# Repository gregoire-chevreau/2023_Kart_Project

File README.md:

# 2023_Kart_Project

Dans ce dossier GitHub, vous trouverez toutes les informations pour continuer le projet.
Ce dernier est composé d'une carte de commande avec la NUCLEO STM32G431RB ainsi que d'un onduleur.

## Table des matières

- [Cahier des charges](#charges)
- [PCB de commande](#commande)
- [Onduleur](#onduleur)
- [Code](#code)

## Cahier des charges

Le but est de faire rouler le kart à 20 km/h.
Le moteur est un moteur OZO 3500W à alimenter en 72 V (https://ozo-electric.com/fr/moteurs-centraux-brushless/679130-moteur-moto-3500w-electrique-central-brushless-bldc.html).
La batterie fourni une tension de  72V (https://ozo-electric.com/fr/72v/282892-batterie-72v-21ah-1512wh-pvc-panasonic-lithium.html#/285-connecteur_de_charge-anderson_pp30/282864-bms-60a_continu_250a_max_compatible_charge_rapide_10a/168358-connecteur_de_puissance-amass_xt90).

## PCB de commande

Ce PCB est composé de la carte NUCLEO, d'une isolation galvanique et d'un level-shifter.
L'isolation galvanique pourra disparaître pour faire un seul PCB commun par la suite. En effet, des optocoupleurs sont prévus comme driver de MOSFET.

## Onduleur

L'onduleur a les caractéristiques suivantes : 
- Tension d'alimentation : 72 V
- Courant nominal : 48 A
De plus, sur cette carte, nous avons prévu une alimentation 15V afin d'alimenter la carte de commande.

## Code

Le code est réalisé avec STM32CubeIDE.
Nous utilisons : 
- 6 sorties GPIO pour commander l’onduleur
- 3 entrées GPIO pour les capteurs Hall
- 1 entrée ADC pour le potentiomètre
- 1 entrée ADC pour le capteur de tension de la batterie
- 1 entrée ADC pour les capteurs de courant de phase

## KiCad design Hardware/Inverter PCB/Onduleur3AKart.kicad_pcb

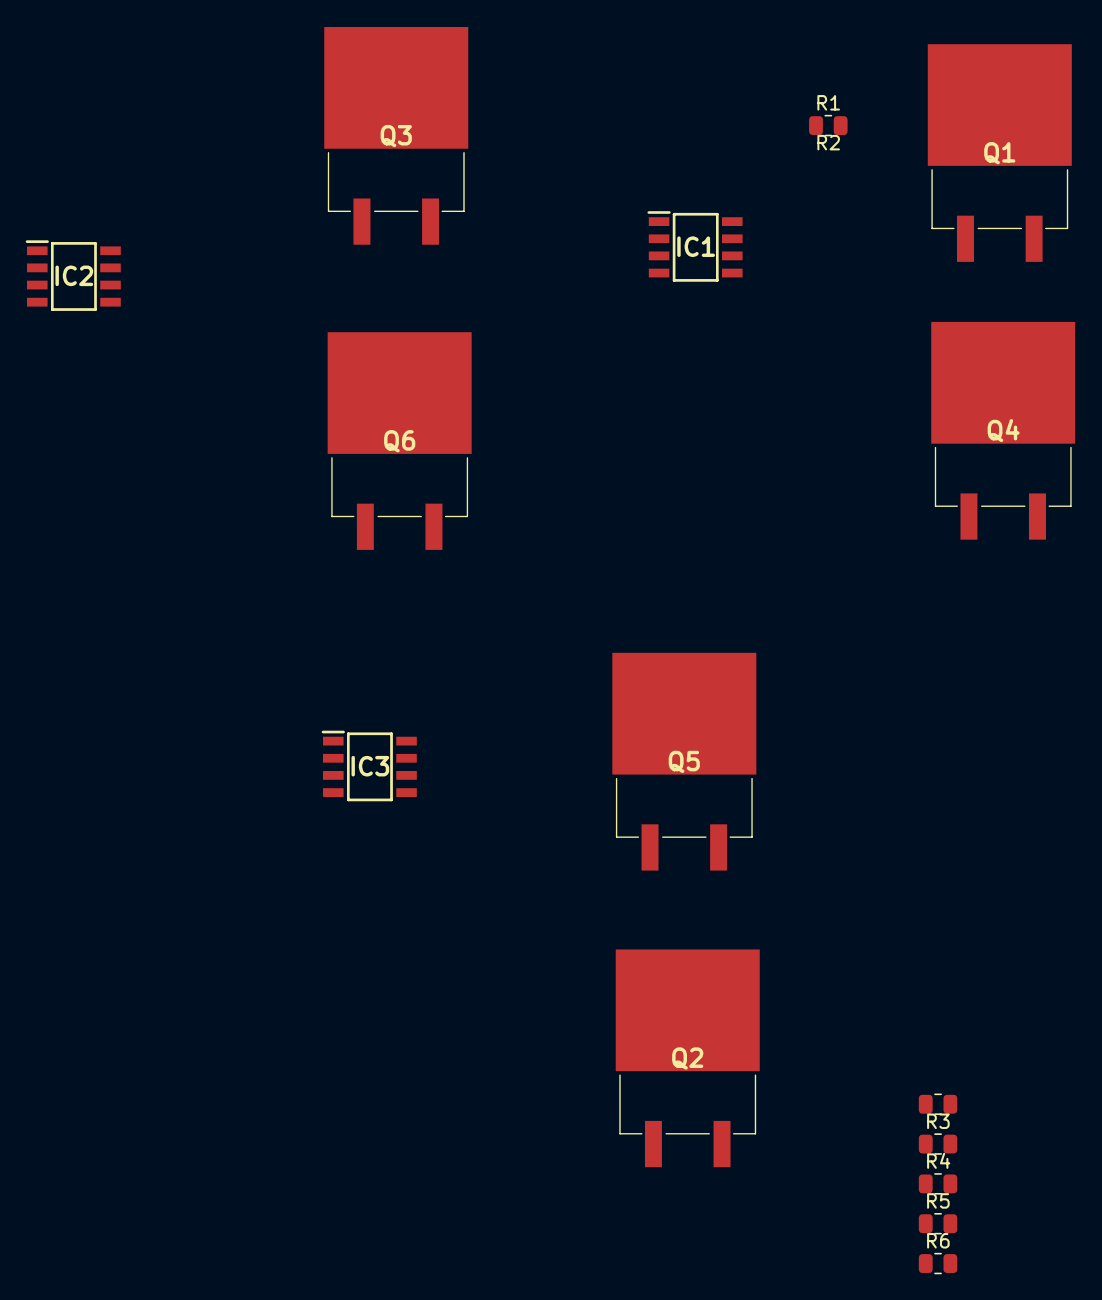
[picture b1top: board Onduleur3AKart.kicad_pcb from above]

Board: 2 copper layers, 15 parts (0 on the bottom side), 15 nets, no tracks yet.

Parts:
IC1, IC2, IC3: TPS2836DR
Q1, Q2, Q3, Q4, Q5, Q6: SUM60N10-17-E3; SUM60N1017E3
R1, R3, R5: 1; R_0805_2012Metric
R2, R4, R6: 5; R_0805_2012Metric

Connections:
unnamed: IC1.6 (BOOTLO), R2.1
unnamed: IC1.7 (HIGHDR), R1.1
unnamed: IC2.6 (BOOTLO), R4.1
unnamed: IC2.7 (HIGHDR), R3.1
unnamed: IC3.6 (BOOTLO), R6.1
unnamed: IC3.7 (HIGHDR), R5.1
unnamed: Q1.1 (G), R1.2
unnamed: Q1.3 (S), Q4.2 (D)
unnamed: Q2.1 (G), R3.2
unnamed: Q2.3 (S), Q5.2 (D)
unnamed: Q3.1 (G), R5.2
unnamed: Q3.3 (S), Q6.2 (D)
unnamed: Q4.1 (G), R2.2
unnamed: Q5.1 (G), R4.2
unnamed: Q6.1 (G), R6.2

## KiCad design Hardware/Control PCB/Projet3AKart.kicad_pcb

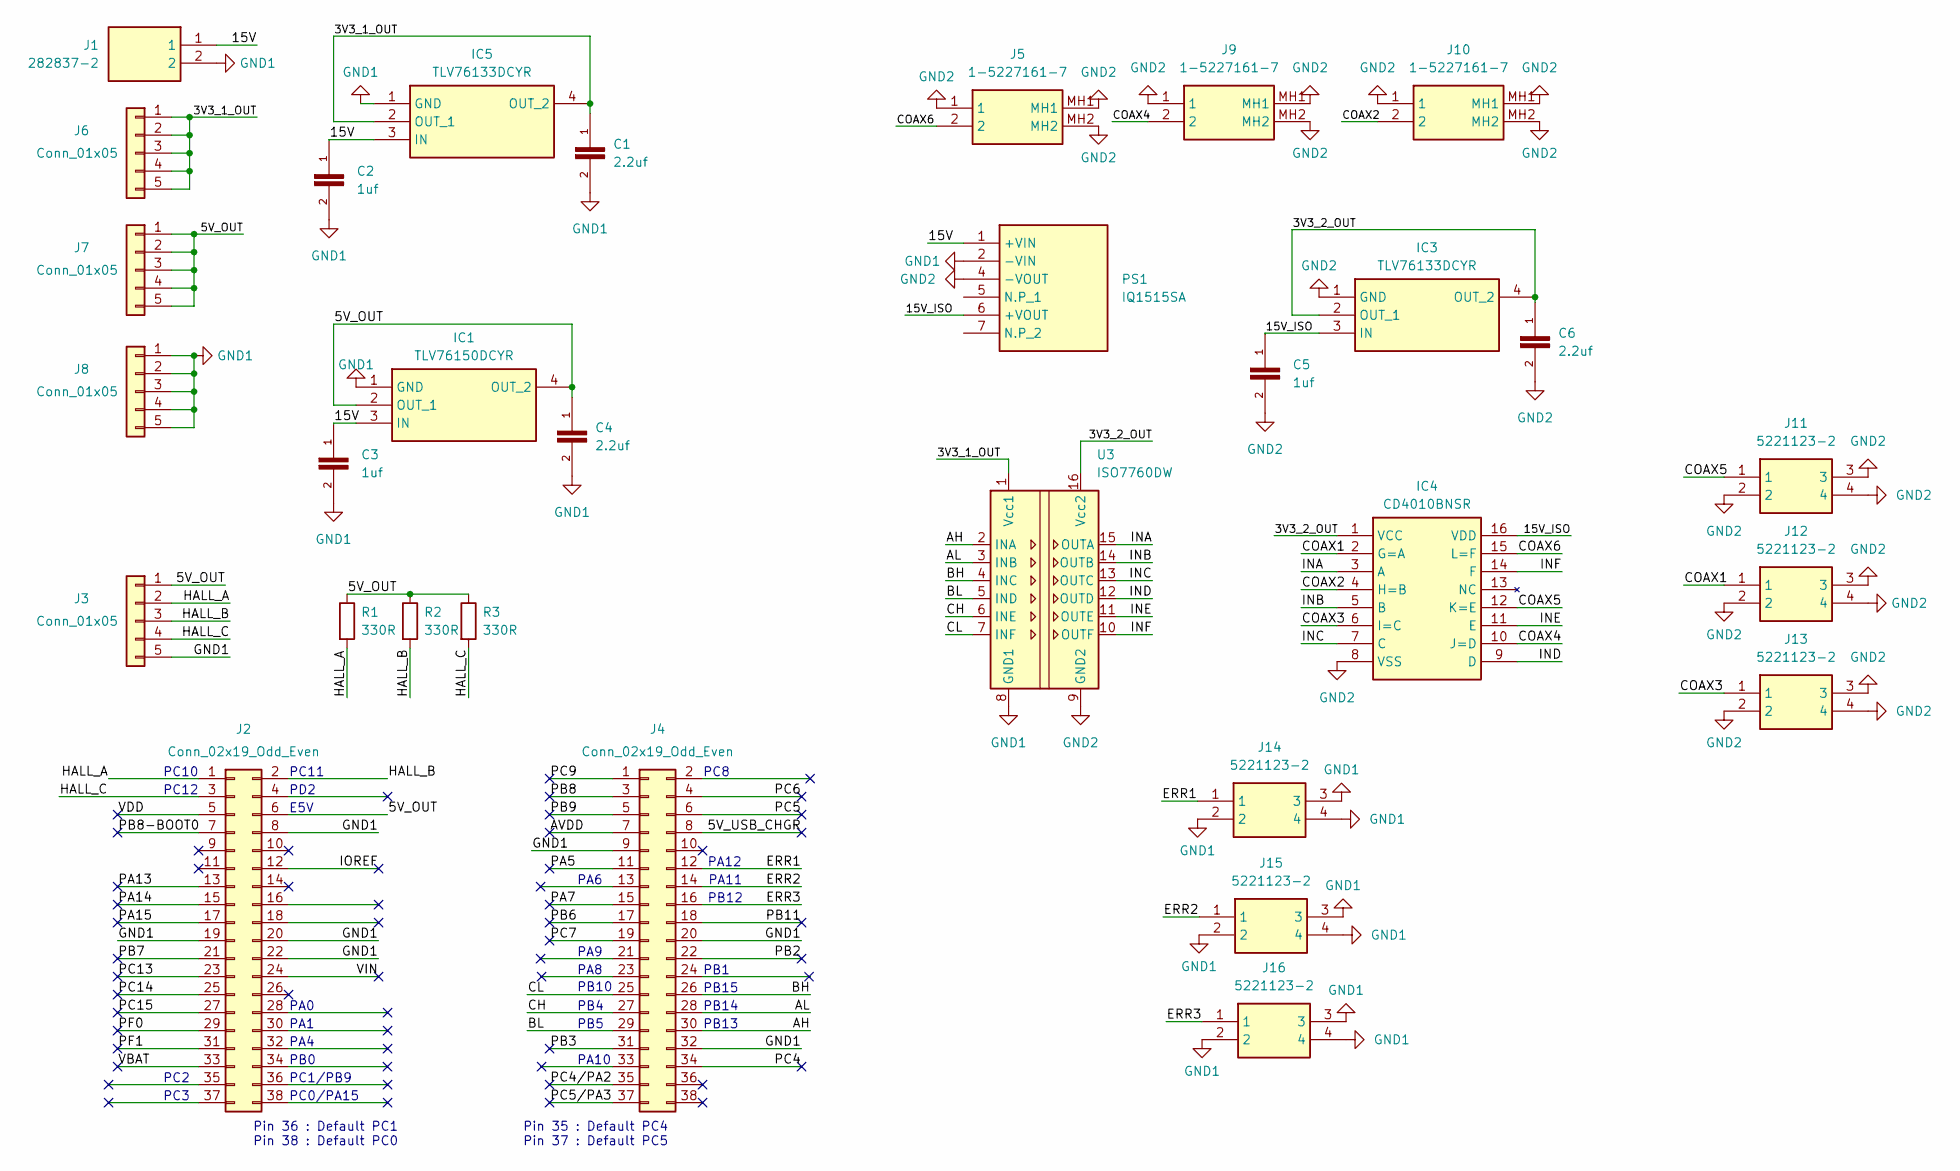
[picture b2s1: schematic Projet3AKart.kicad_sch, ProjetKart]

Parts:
C1, C4, C6: 2.2uf; CAPC2012X140N
C2, C3, C5: 1uf; CAPC2012X140N
IC1: TLV76150DCYR; Mouser Part Number 595-TLV76150DCYR
IC3, IC5: TLV76133DCYR; Mouser Part Number 595-TLV76133DCYR
IC4: CD4010BNSR; Mouser Part Number 595-CD4010BNSR
J1: 282837-2; 2828372; Mouser Part Number 571-2828372
J2, J4: Conn_02x19_Odd_Even; PinHeader_2x19_P2.54mm_Vertical
J3, J6, J7, J8: Conn_01x05; PinHeader_1x05_P2.54mm_Vertical
J5, J9, J10: 1-5227161-7; 152271617; Mouser Part Number 571-1-5227161-7
J11, J12, J13, J14, J15, J16: 5221123-2; 52211232; Manufacturer_Part_Number 5221123-2
PS1: IQ1515SA; Mouser Part Number 209-IQ1515SA
R1, R2, R3: 330R; R_0805_2012Metric
U3: ISO7760DW; SOIC-16W_7.5x10.3mm_P1.27mm

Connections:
/3V3_1_OUT: C1.1, IC5.2 (OUT_1), IC5.4 (OUT_2), J6.1, J6.2, J6.3, J6.4, J6.5, U3.1 (Vcc1)
/3V3_2_OUT: C6.1, IC3.2 (OUT_1), IC3.4 (OUT_2), IC4.1 (VCC), U3.16 (Vcc2)
/5V_OUT: C4.1, IC1.2 (OUT_1), IC1.4 (OUT_2), J2.6, J3.1, J7.1, J7.2, J7.3, J7.4, J7.5, R1.1, R2.1, R3.1
/5V_USB_CHGR: J4.8
/15V: C2.1, C3.1, IC1.3 (IN), IC5.3 (IN), J1.1, PS1.1 (+VIN)
/15V_ISO: C5.1, IC3.3 (IN), IC4.16 (VDD), PS1.6 (+VOUT)
/AH: J4.30, U3.2 (INA)
/AL: J4.28, U3.3 (INB)
/AVDD: J4.7
/BH: J4.26, U3.4 (INC)
/BL: J4.29, U3.5 (IND)
/CH: J4.27, U3.6 (INE)
/CL: J4.25, U3.7 (INF)
/COAX1: IC4.2 (G=A), J12.1
/COAX2: IC4.4 (H=B), J10.2
/COAX3: IC4.6 (I=C), J13.1
/COAX4: IC4.10 (J=D), J9.2
/COAX5: IC4.12 (K=E), J11.1
/COAX6: IC4.15 (L=F), J5.2
/ERR1: J4.12, J14.1
/ERR2: J4.14, J15.1
/ERR3: J4.16, J16.1
/HALL_A: J2.1, J3.2, R1.2
/HALL_B: J2.2, J3.3, R2.2
/HALL_C: J2.3, J3.4, R3.2
/INA: IC4.3 (A), U3.15 (OUTA)
/INB: IC4.5 (B), U3.14 (OUTB)
/INC: IC4.7 (C), U3.13 (OUTC)
/IND: IC4.9 (D), U3.12 (OUTD)
/INE: IC4.11 (E), U3.11 (OUTE)
/INF: IC4.14 (F), U3.10 (OUTF)
/IOREF: J2.12
/PA5: J4.11
/PA7: J4.15
/PA13: J2.13
/PA14: J2.15
/PA15: J2.17
/PB2: J4.22
/PB3: J4.31
/PB6: J4.17
/PB7: J2.21
/PB8: J4.3
/PB8-BOOT0: J2.7
/PB9: J4.5
/PB11: J4.18
/PC4: J4.34
/PC4/PA2: J4.35
/PC5: J4.6
/PC5/PA3: J4.37
/PC6: J4.4
/PC7: J4.19
/PC9: J4.1
/PC13: J2.23
/PC14: J2.25
/PC15: J2.27
/PF0: J2.29
/PF1: J2.31
/VBAT: J2.33
/VDD: J2.5
/VIN: J2.24
GND1: C1.2, C2.2, C3.2, C4.2, IC1.1 (GND), IC5.1 (GND), J1.2, J2.8, J2.19, J2.20, J2.22, J3.5, J4.9, J4.20, J4.32, J8.1, J8.2, J8.3, J8.4, J8.5, J14.2, J14.3, J14.4, J15.2, J15.3, J15.4, J16.2, J16.3, J16.4, PS1.2 (-VIN), U3.8 (GND1)
GND2: C5.2, C6.2, IC3.1 (GND), IC4.8 (VSS), J5.1, J5.MH1, J5.MH2, J9.1, J9.MH1, J9.MH2, J10.1, J10.MH1, J10.MH2, J11.2, J11.3, J11.4, J12.2, J12.3, J12.4, J13.2, J13.3, J13.4, PS1.4 (-VOUT), U3.9 (GND2)

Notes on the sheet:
PB14
PA11
PA8
PB12
PC2
PB5
PA9
PC11
PC12
E5V
PB1
PA4
PB13
PC1/PB9
PB4
PA10
PD2
PC8
PB10
PA6
PB15
PC3
PC10
PA0
PA1
PA12
PB0
Pin 35 : Default PC4 Pin 37 : Default PC5
PC0/PA15
Pin 36 : Default PC1 Pin 38 : Default PC0

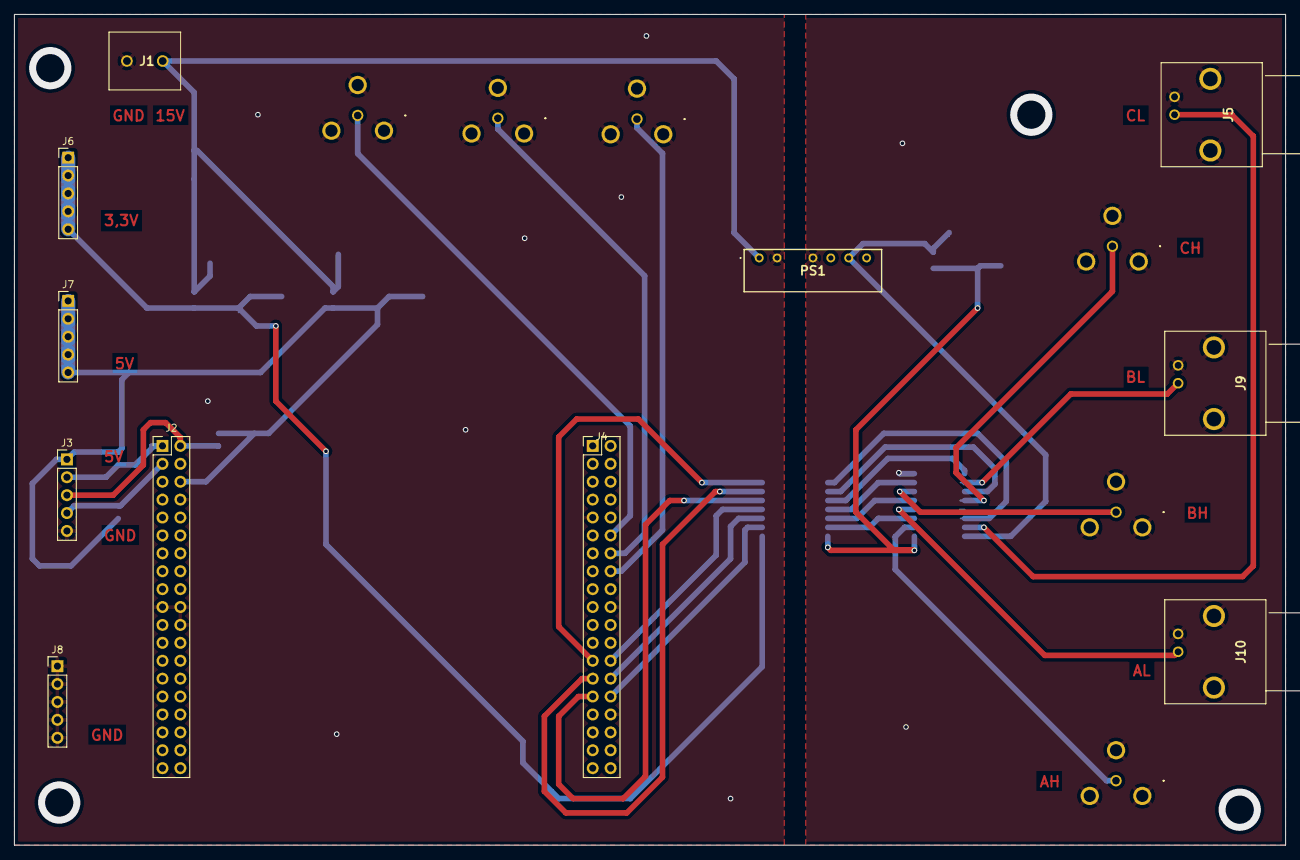
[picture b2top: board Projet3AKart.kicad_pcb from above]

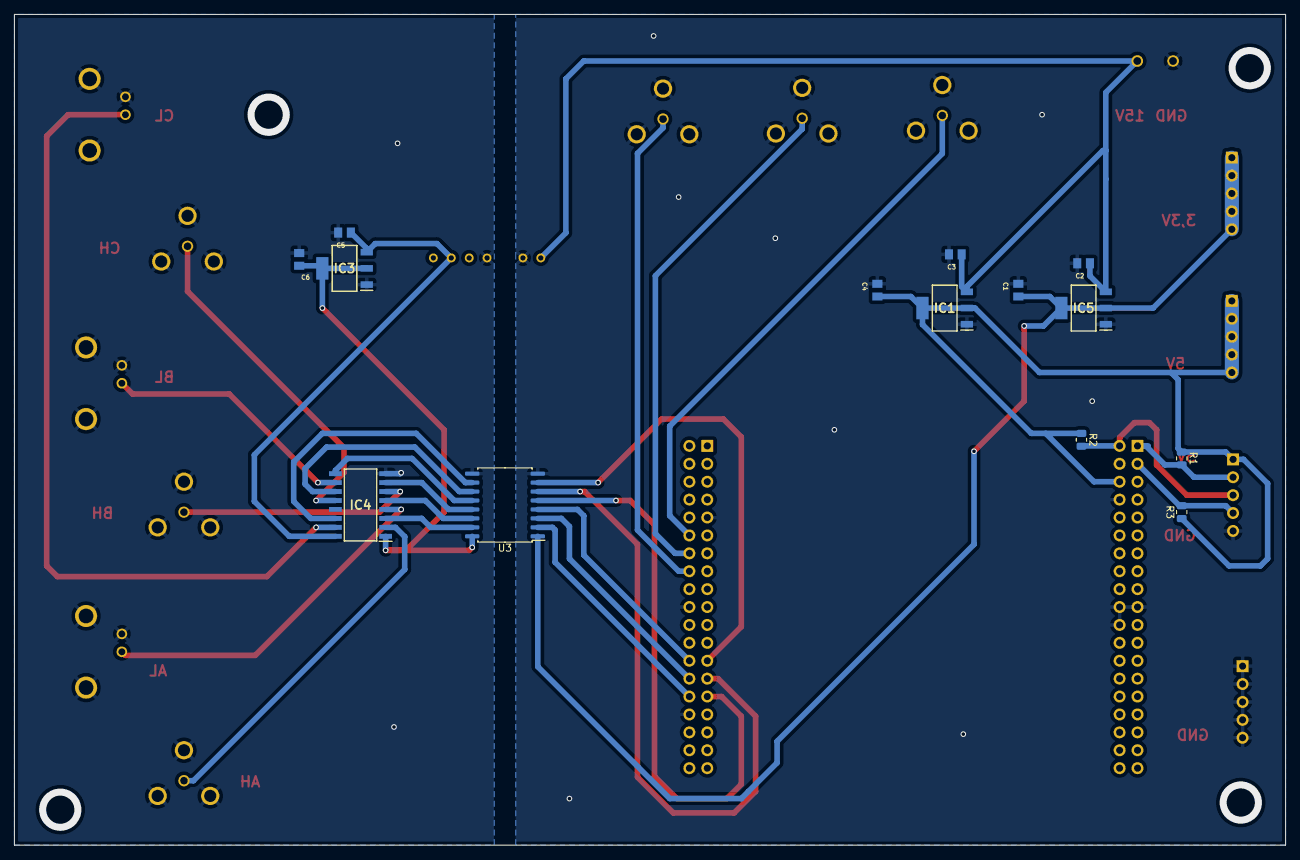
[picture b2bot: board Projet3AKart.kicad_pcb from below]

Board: 2 copper layers, 180.3 x 117.9 mm, 31 parts (14 on the bottom side), 31 nets.

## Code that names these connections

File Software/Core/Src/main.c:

/* USER CODE BEGIN Header */
/**
  ******************************************************************************
  * @file           : main.c
  * @brief          : Main program body
  ******************************************************************************
  * @attention
  *
  * Copyright (c) 2023 STMicroelectronics.
  * All rights reserved.
  *
  * This software is licensed under terms that can be found in the LICENSE file
  * in the root directory of this software component.
  * If no LICENSE file comes with this software, it is provided AS-IS.
  *
  ******************************************************************************
  */
/* USER CODE END Header */
/* Includes ------------------------------------------------------------------*/
#include "main.h"
#include "adc.h"
#include "usart.h"
#include "tim.h"
#include "gpio.h"

/* Private includes ----------------------------------------------------------*/
/* USER CODE BEGIN Includes */
#include "stm32g4xx_hal.h"
#include "math.h"
/* USER CODE END Includes */

/* Private typedef -----------------------------------------------------------*/
/* USER CODE BEGIN PTD */

/* USER CODE END PTD */

/* Private define ------------------------------------------------------------*/
/* USER CODE BEGIN PD */

/* USER CODE END PD */

/* Private macro -------------------------------------------------------------*/
/* USER CODE BEGIN PM */

/* USER CODE END PM */

/* Private variables ---------------------------------------------------------*/

/* USER CODE BEGIN PV */

/* USER CODE END PV */

/* Private function prototypes -----------------------------------------------*/
void SystemClock_Config(void);
/* USER CODE BEGIN PFP */
void MX_GPIO_Init(void);
void Error_Handler(void);
/* USER CODE END PFP */

/* Private user code ---------------------------------------------------------*/
/* USER CODE BEGIN 0 */
uint8_t Hall_A;
uint8_t Hall_B;
uint8_t Hall_C;
/* USER CODE END 0 */

/**
  * @brief  The application entry point.
  * @retval int
  */
int main(void)
{
  /* USER CODE BEGIN 1 */

  /* USER CODE END 1 */

  /* MCU Configuration--------------------------------------------------------*/

  /* Reset of all peripherals, Initializes the Flash interface and the Systick. */
  HAL_Init();

  /* USER CODE BEGIN Init */

  /* USER CODE END Init */

  /* Configure the system clock */
  SystemClock_Config();

  /* USER CODE BEGIN SysInit */

  /* USER CODE END SysInit */

  /* Initialize all configured peripherals */
  MX_GPIO_Init();
  MX_LPUART1_UART_Init();
  MX_TIM1_Init();
  MX_ADC1_Init();
  /* USER CODE BEGIN 2 */

  int value = 0;

  /* USER CODE END 2 */

  /* Infinite loop */
  /* USER CODE BEGIN WHILE */
  while (1)
  {
	  Hall_A = HAL_GPIO_ReadPin(GPIOC, GPIO_PIN_10);
	  Hall_B = HAL_GPIO_ReadPin(GPIOC, GPIO_PIN_11);
	  Hall_C = HAL_GPIO_ReadPin(GPIOC, GPIO_PIN_12);

	  //value = adc_value();
	  value = 1000;
	  PWM(Hall_A, Hall_B, Hall_C);
	  HAL_Delay(value);

	  error;
    /* USER CODE END WHILE */

    /* USER CODE BEGIN 3 */
  }
  /* USER CODE END 3 */
}

/**
  * @brief System Clock Configuration
  * @retval None
  */
void SystemClock_Config(void)
{
  RCC_OscInitTypeDef RCC_OscInitStruct = {0};
  RCC_ClkInitTypeDef RCC_ClkInitStruct = {0};

  /** Configure the main internal regulator output voltage
  */
  HAL_PWREx_ControlVoltageScaling(PWR_REGULATOR_VOLTAGE_SCALE1_BOOST);

  /** Initializes the RCC Oscillators according to the specified parameters
  * in the RCC_OscInitTypeDef structure.
  */
  RCC_OscInitStruct.OscillatorType = RCC_OSCILLATORTYPE_HSI;
  RCC_OscInitStruct.HSIState = RCC_HSI_ON;
  RCC_OscInitStruct.HSICalibrationValue = RCC_HSICALIBRATION_DEFAULT;
  RCC_OscInitStruct.PLL.PLLState = RCC_PLL_ON;
  RCC_OscInitStruct.PLL.PLLSource = RCC_PLLSOURCE_HSI;
  RCC_OscInitStruct.PLL.PLLM = RCC_PLLM_DIV4;
  RCC_OscInitStruct.PLL.PLLN = 85;
  RCC_OscInitStruct.PLL.PLLP = RCC_PLLP_DIV2;
  RCC_OscInitStruct.PLL.PLLQ = RCC_PLLQ_DIV2;
  RCC_OscInitStruct.PLL.PLLR = RCC_PLLR_DIV2;
  if (HAL_RCC_OscConfig(&RCC_OscInitStruct) != HAL_OK)
  {
    Error_Handler();
  }

  /** Initializes the CPU, AHB and APB buses clocks
  */
  RCC_ClkInitStruct.ClockType = RCC_CLOCKTYPE_HCLK|RCC_CLOCKTYPE_SYSCLK
                              |RCC_CLOCKTYPE_PCLK1|RCC_CLOCKTYPE_PCLK2;
  RCC_ClkInitStruct.SYSCLKSource = RCC_SYSCLKSOURCE_PLLCLK;
  RCC_ClkInitStruct.AHBCLKDivider = RCC_SYSCLK_DIV1;
  RCC_ClkInitStruct.APB1CLKDivider = RCC_HCLK_DIV1;
  RCC_ClkInitStruct.APB2CLKDivider = RCC_HCLK_DIV1;

  if (HAL_RCC_ClockConfig(&RCC_ClkInitStruct, FLASH_LATENCY_4) != HAL_OK)
  {
    Error_Handler();
  }
}

/* USER CODE BEGIN 4 */

/* USER CODE END 4 */

/**
  * @brief  This function is executed in case of error occurrence.
  * @retval None
  */
void Error_Handler(void)
{
  /* USER CODE BEGIN Error_Handler_Debug */
  /* User can add his own implementation to report the HAL error return state */
  __disable_irq();
  while (1)
  {
  }
  /* USER CODE END Error_Handler_Debug */
}

#ifdef  USE_FULL_ASSERT
/**
  * @brief  Reports the name of the source file and the source line number
  *         where the assert_param error has occurred.
  * @param  file: pointer to the source file name
  * @param  line: assert_param error line source number
  * @retval None
  */
void assert_failed(uint8_t *file, uint32_t line)
{
  /* USER CODE BEGIN 6 */
  /* User can add his own implementation to report the file name and line number,
     ex: printf("Wrong parameters value: file %s on line %d\r\n", file, line) */
  /* USER CODE END 6 */
}
#endif /* USE_FULL_ASSERT */
